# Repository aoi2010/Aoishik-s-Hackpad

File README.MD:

# Aoishik's Hackpad
My first macropad project! Aoishik's Hackpad is a 6-key macropad designed for coding and music control and a sleek 3D-printed case. Demo Link: [Youtube Demo](https://youtu.be/Q0fAI8v2yJ8)

Case at Light  |  Case at No Light (Glow in the Dark)
:-------------------------:|:-------------------------:
  |  

### Inspiration

I wanted to create a macropad that allowed me to code while listening to music simultaneously. I created a macropad using 6 switches and 1 rp2040. 

### Challenges

Believe it or not, this was my first time using Fusion 360 and KiCad! I watched numerous tutorials and guides and did a TON of googling, but in the end, I'm pretty proud of the final product. I had the most struggle figuring out how to make sketches, and with the new mouse controls, it definitely took me a while to get the hang of it. Also in KiCad, I had a lot of trouble with footprints and making sure everything was aligned properly and the traces were correct(but it became a litle long traces).

### Specifications

BOM: 
- 6x Cherry MX Switches
- 1x XIAO RP2040
- 6x Blank DSA Keycaps
- 4x M3x16 Bolt
- 4x M3 Heatset Inserts

Others:
- ZMK Firmware(.uf2 file)
- PCB Gerber File(PCB/PCB.zip)
- Top and Bottom STL files for 3d Printing

Schematic            |  PCB         |   Case
:-------------------------:|:-------------------------:|:-------------------------:|
    |    | 

### Photos

Case (Separated)     |  PCB & Keycaps
:-------------------------:|:-------------------------:
  |  

With Keycaps         |  Without Keycaps (Switches)
:-------------------------:|:-------------------------:
  |

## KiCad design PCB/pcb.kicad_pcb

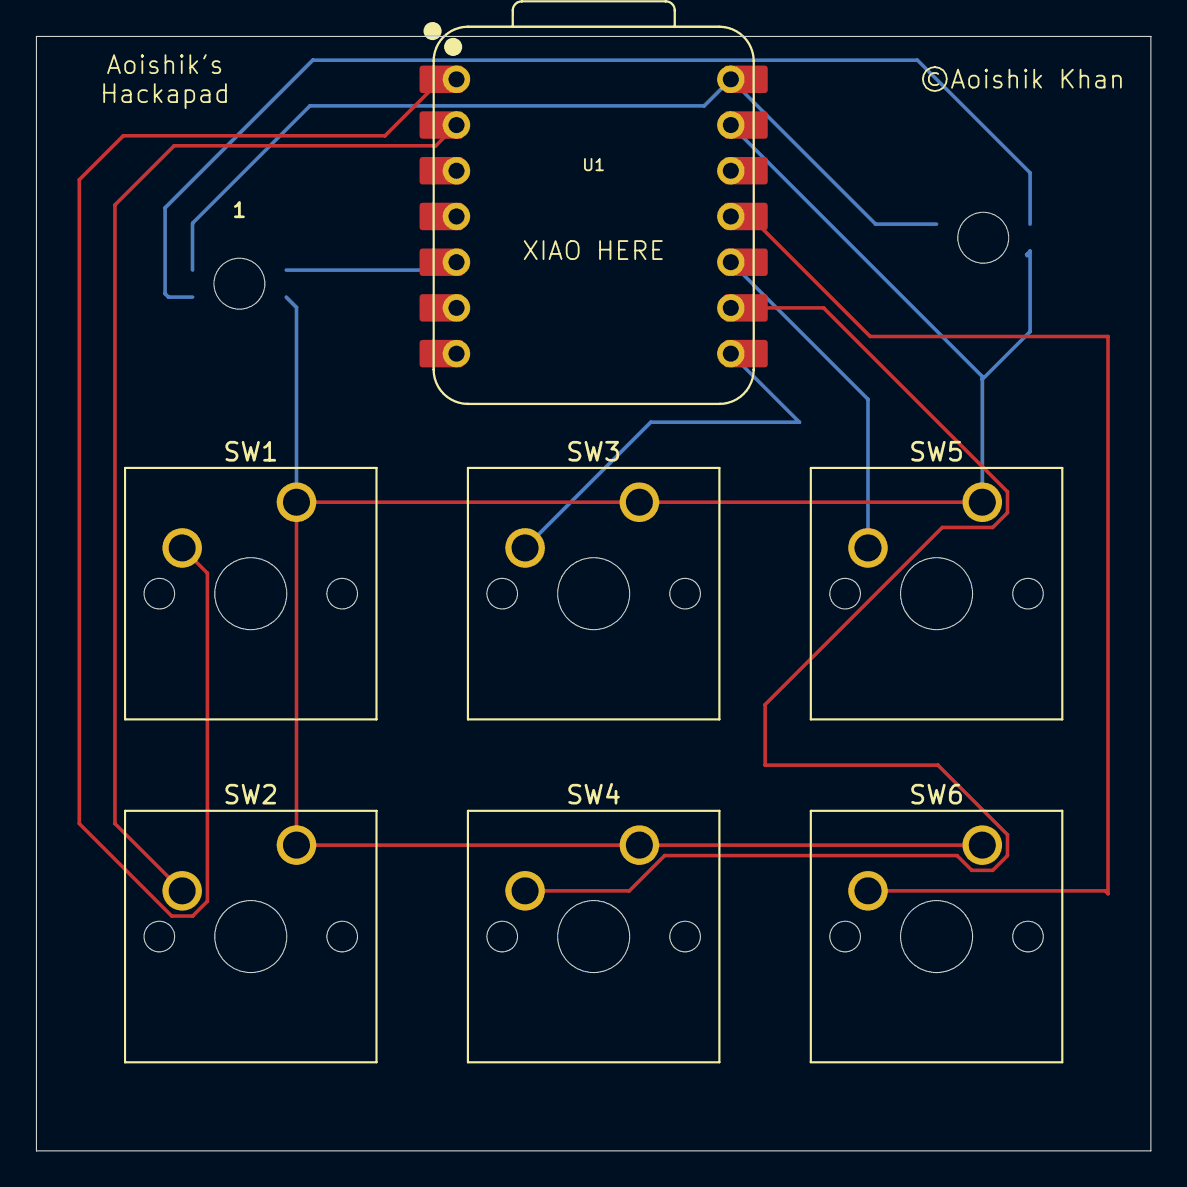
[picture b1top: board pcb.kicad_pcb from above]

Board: 2 copper layers, 61.9 x 61.9 mm, 9 parts (0 on the bottom side), 10 nets.

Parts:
D1, D2: SK6812MINI-E; MX_SK6812MINI-E_REV
SW1, SW2, SW3, SW4, SW5, SW6: SW_Push; SW_Cherry_MX_1.00u_PCB
U1: XIAO-RP2040-DIP

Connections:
+5V: D1.3 (VDD), D2.3 (VDD), U1.14 (VBUS)
GND: D1.1 (VSS), D2.1 (VSS), SW1.1, SW2.1, SW3.1, SW4.1, SW5.1, SW6.1, U1.13 (GND)
unnamed: D1.2 (DIN), U1.5 (GPIO6/SDA)
unnamed: D1.4 (DOUT), D2.2 (DIN)
unnamed: SW3.2, U1.8 (GPIO1/RX)
unnamed: SW4.2, U1.9 (GPIO2/SCK)
unnamed: SW6.2, U1.11 (GPIO3/MOSI)
unnamed: SW5.2, U1.10 (GPIO4/MISO)
unnamed: SW1.2, U1.1 (GPIO26/ADC0/A0)
unnamed: SW2.2, U1.2 (GPIO27/ADC1/A1)

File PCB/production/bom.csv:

Designator,Footprint,Quantity,Value,LCSC Part #
"D1, D2",MX_SK6812MINI-E_REV,2,SK6812MINI-E,
"SW1, SW2, SW3, SW4, SW5, SW6",SW_Cherry_MX_1.00u_PCB,6,SW_Push,
U1,XIAO-RP2040-DIP,1,XIAO-RP2040-DIP,

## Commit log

2026-01-24 Added All The Files
2026-01-24 Added a README
2026-01-24 Fix image paths in README.md
    Updated image paths in README to use forward slashes.
2026-01-24 Changed from SK6812 to SK6812MINI-E
2026-01-25 Changed LEDs
2026-01-25 Update LED specification from SK6812 MINI to MINI-E
2026-01-28 Add initial CAD and PCB design files
    Added BOTTOM.stl and Top.stl files for the CAD design, and PCB.zip for the PCB layout. These files provide the base mechanical and electrical design assets for the project.
2026-01-28 Update README with additional file references
    Added PCB Gerber file and STL files for 3D printing.
2026-01-28 Update keycap description in README
2026-01-31 Add PCB production files; update prefs
    Add generated production outputs and backups for the PCB (bom.csv, designators.csv, netlist.ipc, positions.csv, pcb.zip, and backup zips). Add project preferences file pcb.kicad_prl. Update pcb.kicad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
2026-02-22 Changed firmware from KMK to ZMK for reliability
    Changed firmware from KMK to ZMK for reliability
2026-03-05 Update README: add demo link and photos
    Add YouTube demo link and reorganize README visuals into a photo gallery with captions. Remove the SK6812 LED line from the BOM (project uses 6 switches and 1 RP2040), clarify component list, and imp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

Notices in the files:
PCB/pcb.kicad_pcb:
©Aoishik Khan
